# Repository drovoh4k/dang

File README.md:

# DANG

## Overview
Debido al Covid, ha surgido una necesidad de controlar la cantidad de personas
que hay en los espacios, es decir, el aforamiento.

Debido a esta problemática surge DANG, un sistema de control de aforo en las
clases de mi universidad. Este sistema permite saber cuánta gente hay dentro de
una clase concreta y mantener una trazabilidad de las aulas en las que ha estado
cualquier persona.

## Architecture
El núcleo del proyecto es un Arduino UNO, el cual se comunica con diferentes
módulos.

* **PN532** --> Módulo que nos permite leer tarjetas RFID
* **SSD1306** --> Display Oled de 64x128 píxeles
* **ESP8206** --> Módulo que nos permite conectarnos a una red Wifi y realizar
  conexiones TCP

El proyecto también consta de una página web, la cual se comunica directamente
con el servidor para mostrar el aforo desde un ordenador o dispositivo móvil.

## Prototipe
Las primeras pruebas de software se realizaron sobre protoboard, y una vez se
tenía claro como funcionaba cada módulo y que configuración hardware requería,
se procedió a construir un prototipo.

## PCB
Tras comprobar que el prototipo funcionaba correctamente, se procedió a realizar
la PCB. La cual el esquemático replica completamente el circuito hecho en el
prototipo.

## Web Page
La web todavia se encuentra en fase de pruebas, pero su finalidad es poder ver
el aforo de cada aula en cada momento.

Hasta el momento su aspecto es el siguiente:

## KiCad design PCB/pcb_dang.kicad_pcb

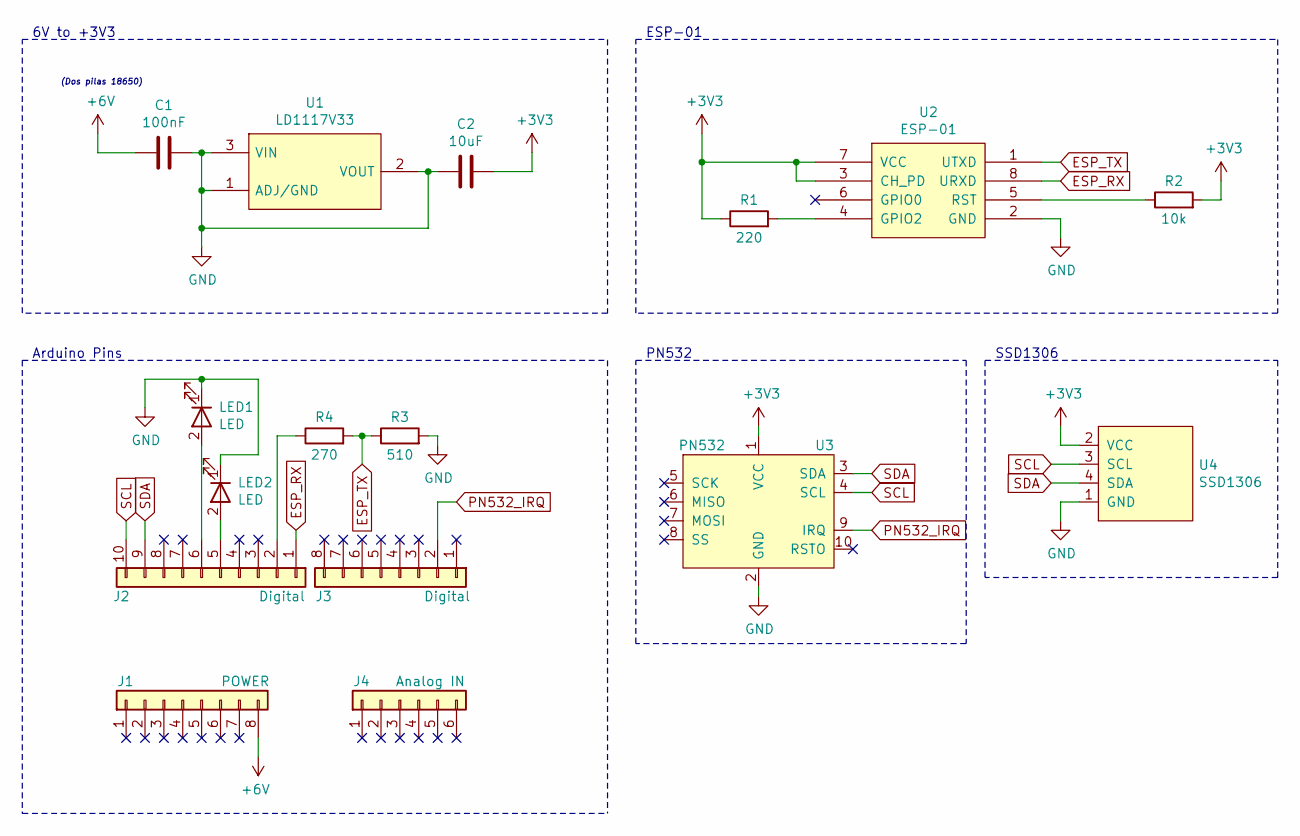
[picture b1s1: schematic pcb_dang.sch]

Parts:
C1: 100nF; C_0603_1608Metric
C2: 10uF; C_0603_1608Metric
J1: POWER; PinHeader_1x08_P2.54mm_Vertical
J2: Digital; PinHeader_1x10_P2.54mm_Vertical
J3: Digital; PinHeader_1x08_P2.54mm_Vertical
J4: Analog IN; PinHeader_1x06_P2.54mm_Vertical
LED1: LED; L1RXGRN1000000000
LED2: LED; L1RXRED1000000000
R1: 220; R_0603_1608Metric
R2: 10k; R_0603_1608Metric
R3: 510; R_0603_1608Metric
R4: 270; R_0603_1608Metric
U1: LD1117V33
U2: ESP-01
U3: PN532
U4: SSD1306

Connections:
+3V3: C2.1, R1.1, R2.2, U2.3 (CH_PD), U2.7 (VCC), U3.1 (VCC), U4.2 (VCC)
+6V: C1.2, J1.8
ESP_RX: J2.1, U2.8 (URXD)
ESP_TX: R3.1, R4.2, U2.1 (UTXD)
GND: C1.1, C2.2, LED1.1, LED2.1, R3.2, U1.1 (ADJ/GND), U1.2 (VOUT), U1.3 (VIN), U2.2 (GND), U3.2 (GND), U4.1 (GND)
unnamed: J2.2, R4.1
unnamed: J2.5, LED2.2
unnamed: J2.6, LED1.2
unnamed: R1.2, U2.4 (GPIO2)
unnamed: R2.1, U2.5 (RST)
PN532_IRQ: J3.2, U3.9 (IRQ)
SCL: J2.10, U3.4 (SCL), U4.3 (SCL)
SDA: J2.9, U3.3 (SDA), U4.4 (SDA)

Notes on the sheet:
(Dos pilas 18650)
6V to +3V3
Arduino Pins
ESP-01
SSD1306
PN532

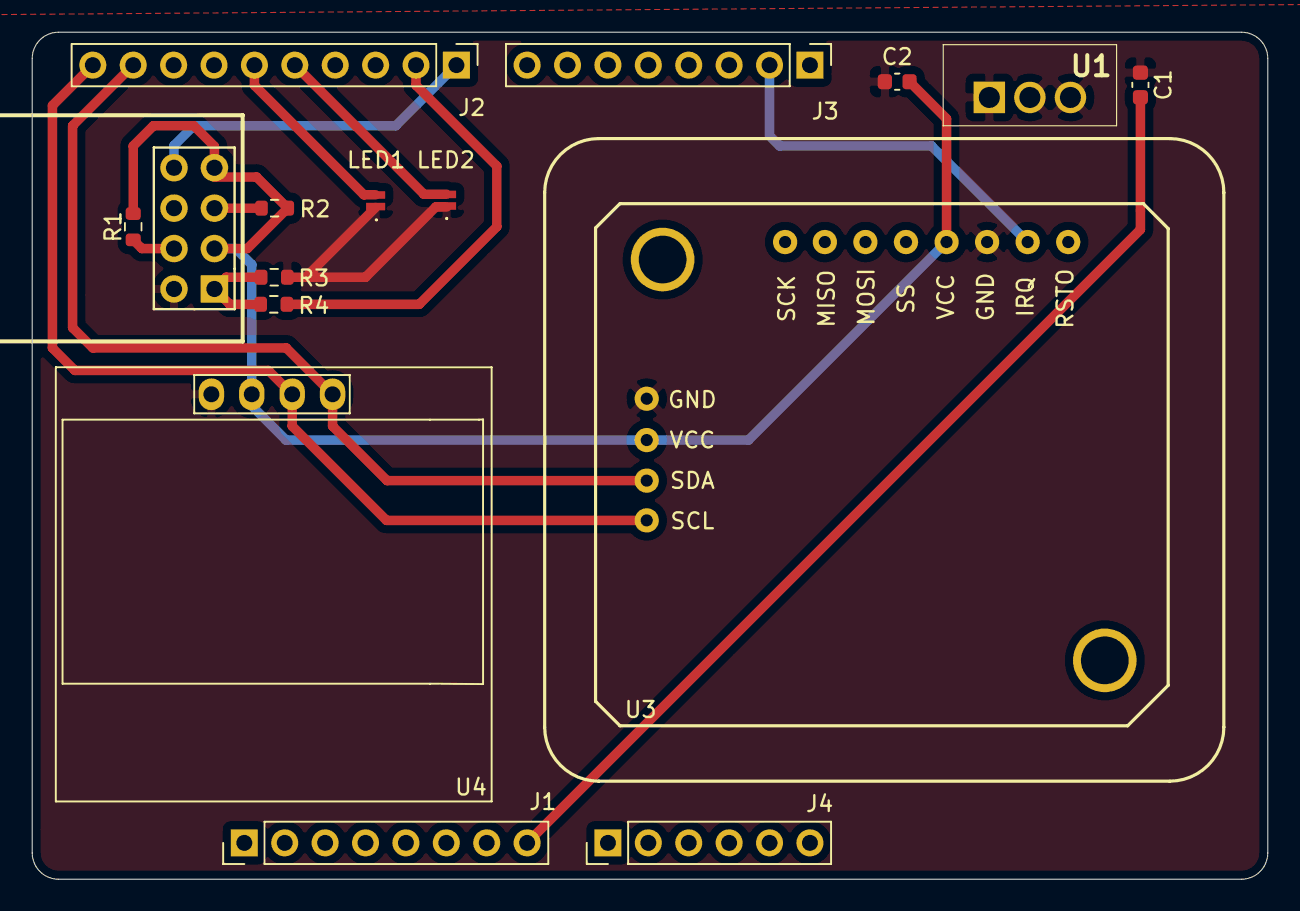
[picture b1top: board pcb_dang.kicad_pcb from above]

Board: 2 copper layers, 77.7 x 53.3 mm, 16 parts (0 on the bottom side), 13 nets.

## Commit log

2022-06-08 README created
2022-06-08 README updated
2022-06-08 old README removed
2022-06-08 Arduino code added
2022-06-08 servidor code added
2022-06-08 demo web code added
2022-06-08 PCB project added
